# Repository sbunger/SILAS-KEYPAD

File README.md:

# SILAS' KEYPAD
Silas' hackpad project created with help from Hackclub! This macropad has eight keys that are currently programmed to control browser and copy/paste functions, but can be programmed with other keys and even macros. The pad runs on an RP2040 devboard by Seeed Studio. The PCBs were created in KICAD and the CAD files were made in Fusion. I used the KMK library to program my keyboard.

I created this macropad to gain experience in electronics while making something cool that I will actually use. Currently, the keys are as follows from left to right: Row 1: Copy, Paste, Cut, Ctrl-Alt-Del; Row 2: New Tab, Close Tab, Reopen Closed Tab, and new firefox window (requires custom shortcut on windows).

## Bill of Materials
- **8x** M3x5mx4mm heatset inserts
- **8x** M3x16mm screws
- **2x** SK6812 MINI-E LEDs
- **8x** Cherry MX Switches (Or equivilant)
- **8x** Blank DSA keycaps
- **8x** Through-hole 1N4148 Diodes
- **1x** 3d Printed Case (Self Printing)
- **1x** Manufactured PCB
- **1x** Seeed XIAO RP2040
## Cad
All cad was created in Fusion 360 Education. I really enjoyed using bevels on the edges to make it feel truely polished. All holes in the base will be fitted with threaded inserts and the holes will use M3 nuts and bolts.

## PCB
PCBs were created in KICAD.

## Renders
Renders were created in Fusion and Blender.

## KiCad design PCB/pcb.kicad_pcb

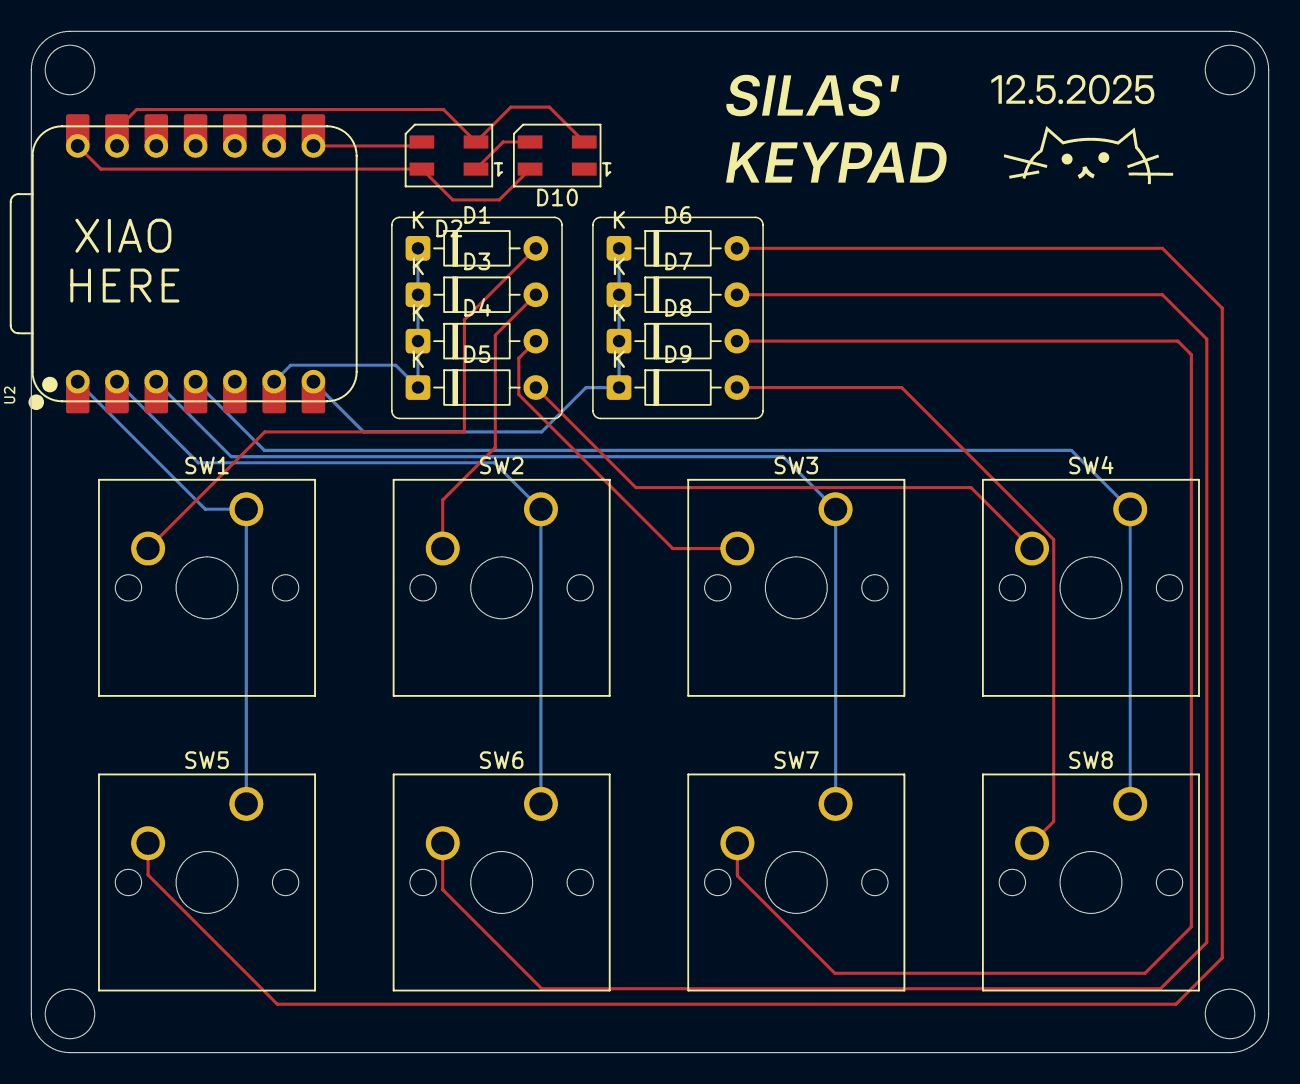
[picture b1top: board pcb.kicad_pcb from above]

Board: 2 copper layers, 80.0 x 66.0 mm, 19 parts (0 on the bottom side), 18 nets.

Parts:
D1, D3, D4, D5, D6, D7, D8, D9: 1N4148; D_DO-35_SOD27_P7.62mm_Horizontal
D2, D10: SK6812MINI; LED_SK6812MINI_PLCC4_3.5x3.5mm_P1.75mm
SW1, SW2, SW3, SW4, SW5, SW6, SW7, SW8: SW_Push; SW_Cherry_MX_1.00u_PCB
U2: XIAO-RP2040-DIP

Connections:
+5V: D2.4 (VDD), D10.4 (VDD), U2.14 (VBUS)
Col0: SW1.1, SW5.1, U2.1 (GPIO26/ADC0/A0)
Col1: SW2.1, SW6.1, U2.2 (GPIO27/ADC1/A1)
Col2: SW3.1, SW7.1, U2.3 (GPIO28/ADC2/A2)
Col3: SW4.1, SW8.1, U2.4 (GPIO29/ADC3/A3)
GND: D2.2 (VSS), D10.2 (VSS), U2.13 (GND)
LED: D2.3 (DIN), U2.8 (GPIO1/RX)
unnamed: D1.2 (A), SW1.2
unnamed: D3.2 (A), SW2.2
unnamed: D4.2 (A), SW3.2
unnamed: D5.2 (A), SW4.2
unnamed: D6.2 (A), SW5.2
unnamed: D7.2 (A), SW6.2
unnamed: D8.2 (A), SW7.2
unnamed: D9.2 (A), SW8.2
unnamed: D2.1 (DOUT), D10.3 (DIN)
Row0: D1.1 (K), D3.1 (K), D4.1 (K), D5.1 (K), U2.6 (GPIO7/SCL)
Row1: D6.1 (K), D7.1 (K), D8.1 (K), D9.1 (K), U2.7 (GPIO0/TX)

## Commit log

2025-12-06 all files added
2025-12-07 Final Readme
2025-12-07 Uploader Gerber and Drill foles
2025-12-16 Blender file added, render created
2025-12-16 fixed large files
2025-12-18 redner
2026-01-02 Updated firmware to final, added updated cad files
2026-01-02 Revise README with updated project details
    Updated project description and added new sections for renders and PCB details.
2026-01-23 Refactor README formatting and image sizes
    Updated formatting and improved image widths in README.
